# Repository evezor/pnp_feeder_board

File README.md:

# pnp_feeder_board
Pnp Feeder Edge Board

See more about this board and Tobor here: http://crowdsupply.evezor.com

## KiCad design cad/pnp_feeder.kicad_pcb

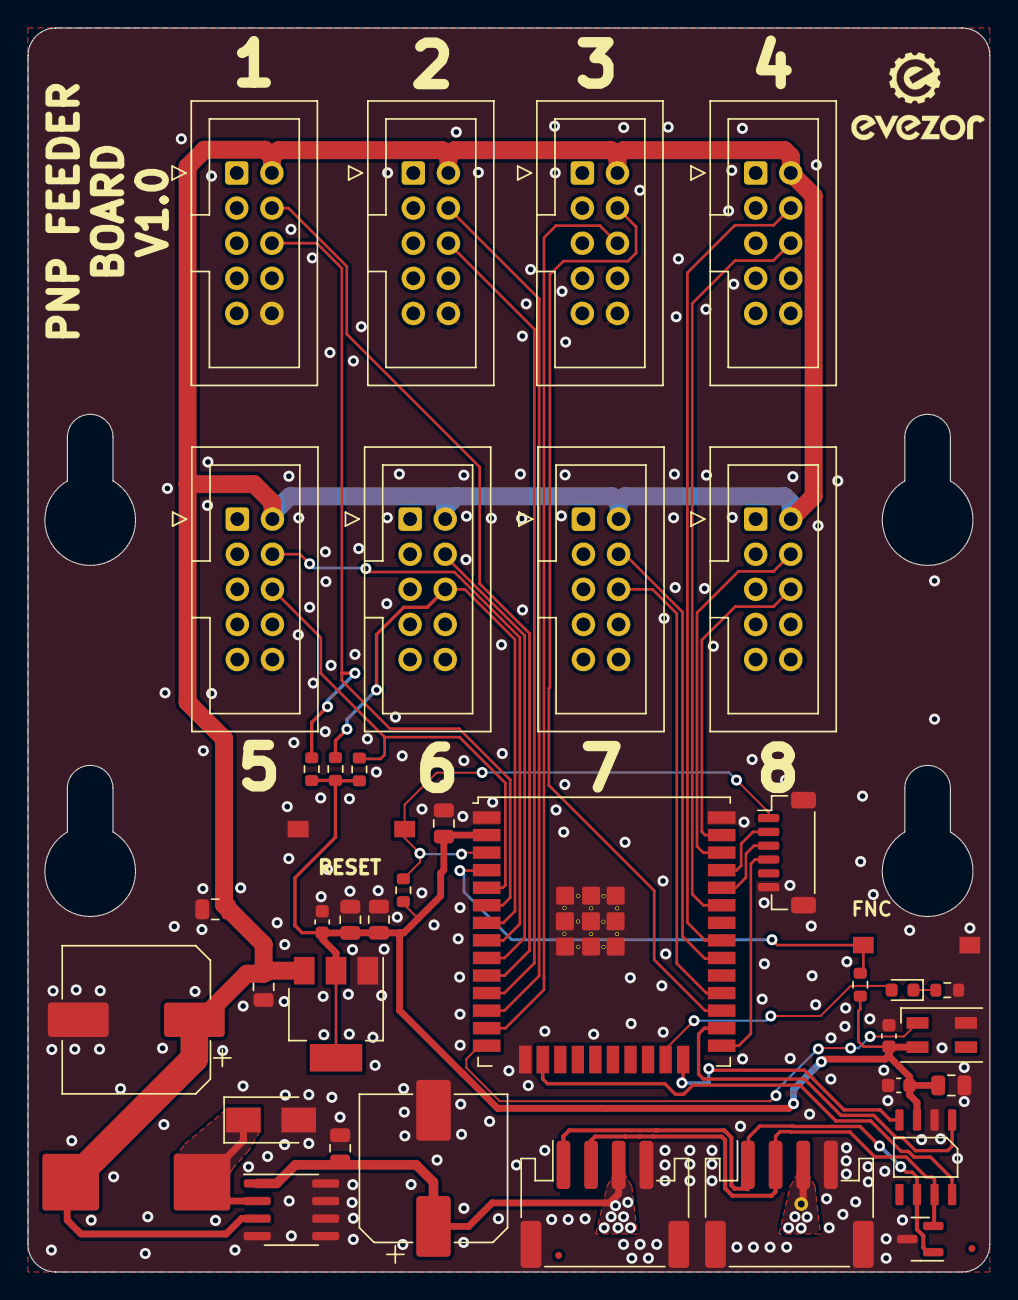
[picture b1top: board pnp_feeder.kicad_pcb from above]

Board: 2 copper layers, 69.6 x 90.0 mm, 43 parts (1 on the bottom side), 34 nets.

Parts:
C101, C105: 220uF; CP_Elec_10x10.5
C102, C107: 4.7uF 100V; C_0805_2012Metric
C103, C104, C106, C108, C111: 22uF; C_0805_2012Metric
C109, C110, C112: .1uF; C_0603_1608Metric
D101: SX35_SCHOTTKY; D_SMA
D102: D_TVS_x2_AAC; SOT-23
D103: led_g; LED_0603_1608Metric
D104: SK6812MINI; LED_SK6812MINI_PLCC4_3.5x3.5mm_P1.75mm
FID101, FID102: Fiducial; Fiducial_0.5mm_Mask1mm
J101, J102, J103, J104, J105, J106, J107, J108: Conn_02x05_Odd_Even; IDC-Header_2x05_P2.54mm_Vertical
J109, J110: Conn_01x04; JST_PH_S4B-PH-SM4-TB_1x04-1MP_P2.00mm_Horizontal
J111: ftdi_conn; JST_SH_BM06B-SRSS-TB_1x06-1MP_P1.00mm_Vertical
L101: 68uF; INDUCTOR-68uH
R101, R102, R103, R104, R105, R106: 10k; R_0603_1608Metric
SW101, SW102: SW_Push; SWITCH_2x3_SMD_TACTILE_GREEN
TP1: TestPoint; TestPoint_THTPad_D1.0mm_Drill0.5mm
U101: XL1509; SOIC-8_3.9x4.9mm_P1.27mm
U102: ESP32-WROOM-32U; ESP32-WROOM-32U_evezor
U103: AMS1117-3.3; SOT-223-3_TabPin2
U104: Trans_CAN_SN65HVD230DR; CAN-TRANS-SN65HVD230DR

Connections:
+3V3: C103.1, C104.1, C106.1, C109.1, C110.1, C111.1, C112.2, D104.4 (VDD), R101.2, R102.2, R103.2, R104.2, R105.2, U102.2 (VDD), U103.2 (VO), U104.3 (Vcc)
+5V: C105.1, C107.1, C108.1, J101.2, J102.2, J103.2, J104.2, J105.2, J106.2, J107.2, J108.2, L101.1, U101.3 (FEEDBACK), U103.3 (VI)
/BOOT: J111.4, U102.25 (BOOT-A2-IO0)
/CAN_H: D102.2 (A2), J109.2, J110.2, U104.7 (CANH)
/CAN_L: D102.1 (A1), J109.1, J110.1, U104.6 (CANL)
/CAN_RX: U102.24 (LOW@BOOT-A2-IO2), U104.4 (R)
/CAN_SLP: U102.16 (HMOSI-A2-IO13), U104.8 (Rs)
/CAN_TX: U102.26 (A2-IO4), U104.1 (D)
/FUNCTION_BUTTON: R105.1, SW101.1, U102.4 (SENSOR_VP-IO36-A1-inputOnly-noPU)
/HBT_LED: D103.2 (A), U102.23 (NOISE@BOOT-A2-IO15)
/NEO_STATUS: D104.3 (DIN), U102.14 (LOW@BOOT-HMISO-A2-IO12)
/RESET: J111.1, R102.1, SW102.1, U102.3 (EN)
/RXD0: J111.3, U102.34 (RXD0/IO3)
/TXDO: J111.2, U102.35 (TXD0/IO1)
/button_1: J101.6, R104.1, U102.6 (inputOnly-noPU-A1-IO34)
/button_2: J105.6, U102.11 (SDA1-DAC2-A2-IO26)
/button_3: J102.6, U102.13 (NOISE@BOOT-HSCK-A2-IO14)
/button_4: J106.6, U102.33 (IO21)
/button_5: J103.6, R101.1, U102.5 (SENSOR_VN-IO39-A1-inputOnly-noPU)
/button_6: J107.6, R103.1, U102.7 (inputOnly-noPU-A1-IO35)
/button_7: J104.6, U102.28 (IO17)
/button_8: J108.6, U102.37 (VMOSI-IO23)
/servo_1: J101.4, U102.10 (SCL1-DAC1-A2-IO25)
/servo_2: J105.4, U102.12 (A2-IO27)
/servo_3: J102.4, U102.27 (IO16)
/servo_4: J106.4, U102.31 (SDA0-VMISO-IO19)
/servo_5: J103.4, U102.8 (A1-IO32)
/servo_6: J107.4, U102.9 (A1-IO33)
/servo_7: J104.4, U102.30 (SCL0-VCLK-IO18)
/servo_8: J108.4, U102.36 (IO22)
GND: C101.2, C102.2, C103.2, C104.2, C105.2, C106.2, C107.2, C108.2, C109.2, C110.2, C111.2, C112.1, D101.2 (A), D102.3 (common), D104.2 (VSS), J101.10, J102.10, J103.10, J104.10, J105.10, J106.10, J107.10, J108.10, J109.4, J109.MP (MountPin), J110.4, J110.MP (MountPin), J111.6, J111.MP (MountPin), R106.1, SW101.2, SW102.2, U101.4 (ON/OFF), U101.5 (GND), U101.6 (GND), U101.7 (GND), U101.8 (GND), U102.1 (GND), U102.15 (GND), U102.38 (GND), U102.39 (GND), U103.1 (GND), U104.2 (GND)
unnamed: D101.1 (K), L101.2, U101.2 (OUTPUT)
unnamed: D103.1 (K), R106.2
VBUS: C101.1, C102.1, J109.3, J110.3, TP1.1, U101.1 (VIN)

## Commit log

2025-01-09 init
2025-01-09 add more pics and readme and license
